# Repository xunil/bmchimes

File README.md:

Controller firmware for ESP8266 modules for Burning Man chimes project.

Using RtcDS3231 library https://github.com/Makuna/Rtc/

TODO:
* WiFi improvements
  * Add config keys for at least 3 WiFi networks and SSIDs
  * Attempt to join each in series for 20 seconds at a time
  * If all three fail, become AP instead
  * Add option to go straight to AP mode
* Add ADC measurement and recording for battery voltage
* Defaults for config

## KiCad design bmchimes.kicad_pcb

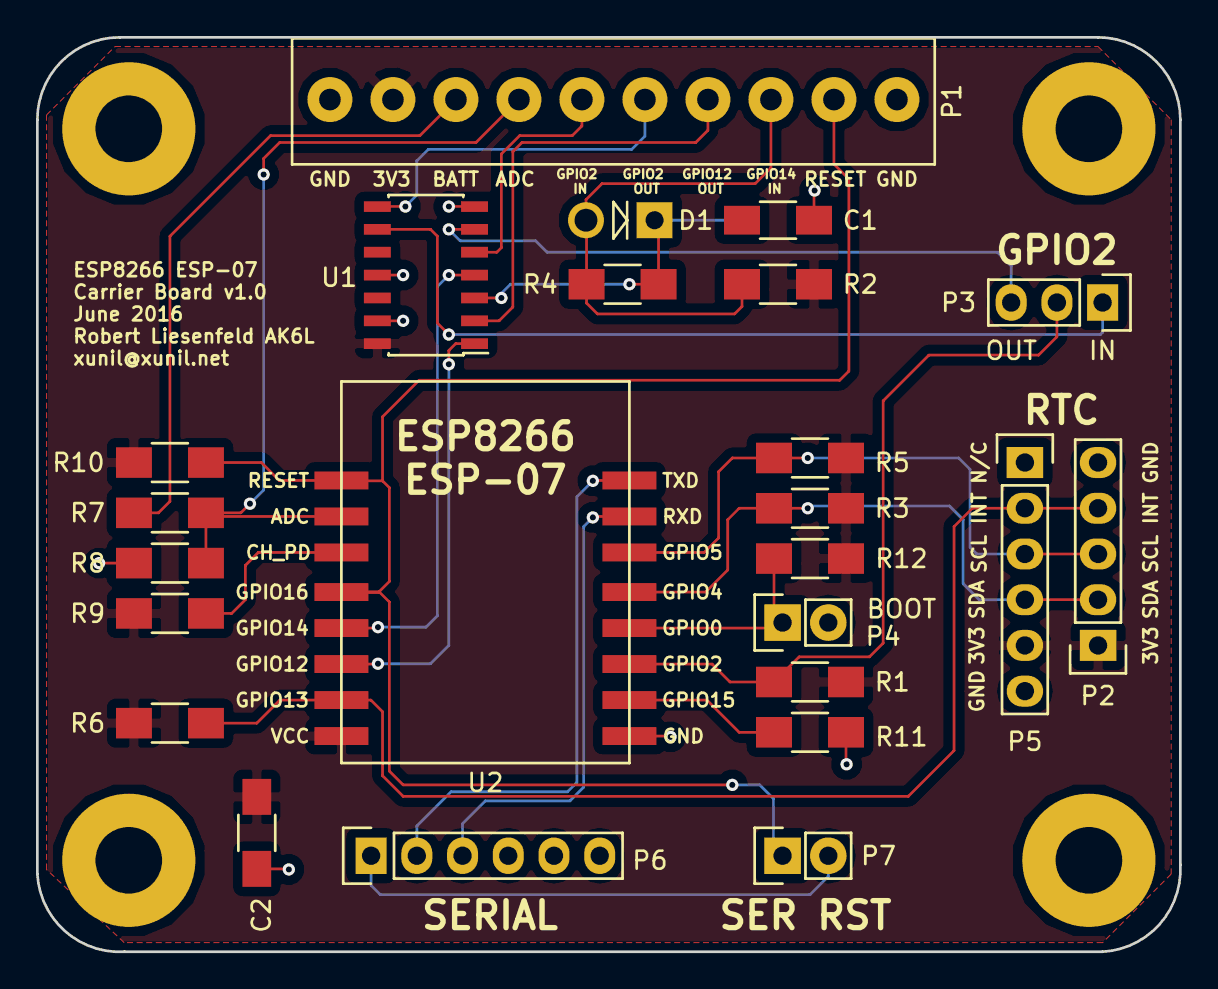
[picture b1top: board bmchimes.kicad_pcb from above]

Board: 2 copper layers, 63.5 x 50.8 mm, 28 parts (0 on the bottom side), 24 nets.

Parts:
C1, C2: C; C_1206_HandSoldering
D1: D; Diode_DO-41_SOD81_Vertical_AnodeUp
P1: CONN_01X10; Adafruit_3.5mm_Terminal_Block
P2: CONN_01X05; Pin_Header_Straight_1x05
P3: CONN_02X03; Pin_Header_Straight_1x03
P4, P7: CONN_01X02; Pin_Header_Straight_1x02
P5, P6: CONN_01X06; Pin_Header_Straight_1x06
P8, P9, P10, P11: CONN_01X01; MountingHole_3.7mm_Pad
R1, R2, R3, R4, R5, R6, R7, R8, R9, R10, R11, R12: R; R_1206_HandSoldering
U1: 74HC7014; SOIC-14_3.9x8.7mm_Pitch1.27mm
U2: ESP07

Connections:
3V3: C2.1, P1.2, P2.1, P5.5, R1.1, R2.2, R3.1, R5.1, R6.1, R9.1, R10.1, R12.1, U1.14, U2.16
ADC: P1.4, R7.2, R8.1, U2.10
BATT: P1.3, R7.1
GND: C1.2, C2.2, P1.1, P1.10, P2.5, P4.2, P5.6, P6.6, P8.1, P9.1, P10.1, P11.1, R8.2, R11.2, U1.7, U1.11, U1.13, U2.1
GPIO2: P3.2, R1.2, U2.3
GPIO2_IN: P1.5, U1.5
GPIO2_IN_ST: P3.3, U1.6
GPIO2_OUT: P3.1, U1.9
GPIO2_OUT_ST: P1.6, U1.8
GPIO4: P2.2, P5.4, R3.2, U2.5
GPIO5: P2.3, P5.3, R5.2, U2.6
GPIO12: U1.1, U2.14
GPIO12_OUT: P1.7, U1.2
GPIO13: P2.4, P5.2, R6.2, U2.15
GPIO14: U1.4, U2.13
GPIO14_IN: D1.2, P1.8, R2.1, R4.2
GPIO14_IN_DB: C1.1, D1.1, R4.1, U1.3
unnamed: P4.1, R12.2, U2.4
unnamed: R9.2, U2.11
unnamed: R11.1, U2.2
RESET: P1.9, P7.1, R10.2, U2.9, U2.12
RESET_SER: P6.1, P7.2
RXD: P6.3, U2.7
TXD: P6.2, U2.8

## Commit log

2016-03-29 Initial import: Lots of basic functionality working. Need to add scheduled GPIO triggering.
2016-03-29 Switched to Rtc library from https://github.com/Makuna/Rtc
2016-04-08 Config read from SPIFFS working
2016-04-10 Added config write, status page, reset button
2016-04-11 Added device description field, chime offset field, home buttons; reset page now refreshes automatically
2016-04-13 Beginning to add sleep and chime timing
2016-04-14 WIP: Sleep and chime timing
2016-04-15 WIP: Still trying to figure out wake/sleep cycle timing
2016-04-22 Updated TODOs, generalized time string construction
2016-04-24 WIP: Calculating wake and sleep
2016-05-01 Finally have RTC alarm working, and sleep alarm calculation appears to be functional as well.
2016-05-10 Finishing up this branch, which has incorporated far more than just config parsing.
2016-05-12 Now using alarm 2 for chime indication; first stab at making sure we're not asleep when it's time to chime
2016-05-15 Fixing compile errors
2016-05-24 Chime timing and stop switch detection is working.
2016-05-25 Fixed bug in handleConfig with handling of checkboxes.
2016-05-30 First effort at a carrier board for the ESP07.
2016-06-01 Added buffer chip to schematic
2016-06-04 ERC passes
2016-06-04 WIP: Pin header layout
2016-06-06 Reworked some of the pull-ups and re-annotated.
2016-06-07 Added footprint for ESP07
2016-06-09 Basic layout complete, ground and power zones defined.
2016-06-10 Zero unconnected nets, calling it done
2016-06-11 Silkscreen changes, sent board to OSH Park
2016-06-15 Added values, ordered parts
2016-06-27 Builds but fundamentally flawed logic: Need to return to RTC alarm-based chime timing and use once-a-minute alarm for non-critical events such as sleep and statistics tracking
2016-06-27 Option-izing the chime stop chiming
2016-06-27 Switched back to chimes being triggered by an RTC alarm; still need to add chime repetition and hours chiming; sleeping and stats collection triggered by once-per-minute alarm.
2016-07-01 Many fixes and features: - Separated chiming back onto its own alarm. - Added chime testing page. - Added default config when config not found on SPIFFS. - Added WiFi AP mode. - Default configuration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
2016-07-01 Minor fixes to debug output; added logic to skip a scheduled chime if a manual one is in progress; fixed issue with AP mode.
2016-07-03 Removed some superfluous debugging info and added an automatic refresh to the stats page.
2016-07-04 - Updated root page to display next chime, next sleep, and correct temperature. - Syncing with NTP and writing to RTC will now cause sleep and chime timing to be recalculated. - Added ability to clea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
2016-07-05 No idea why, but twiddling the LED in the stop switch ISR seems to have fixed the issue.
2016-07-06 Don't handle web requests while chiming as it interferes with interrupt response times, such as for the chime stop switch.
2016-07-06 Added chime duration stats collection.
2016-07-06 Fixed statistics collection for chime duration.
2016-07-19 Turns out rewriting a 1400+ line file to slow flash takes about 5 or 6 seconds, so we just won't do that while chiming. Future enhancement: set a flag to collect stats, collect after chime finished.
2016-07-22 Removed some unnecessary headers, switched from #defines to consts, rearranged some header includes, and got the heartbeat working (sort of).
2016-07-23 Fixing stats collection bug
2016-07-24 Maybe we can handle web requests while chiming after all.
2016-07-30 Heartbeat blip now fires every 15 sec.
2016-07-30 Ad hoc network now starts with a password
2016-07-30 Added sanity check so the module never goes into a permanent sleep.
2016-07-31 Bugfixes and added configuration options, including: - Added config option to enable/disable heartbeat LED on pin 2 - Added config option for inter-chime delay, in preparation for sequential chime - 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
2016-08-01 All timing in seconds (except for stop switch timeout, which is in ms), also added chime sequence and hour chime.
2016-08-02 Updating example config to reflect updated options
2016-08-04 First stab at absolute timing for the chime delays; the chimes should start N seconds after the last chime started, not after the last chime -ended-
2016-08-06 Switched to model where chime schedule is calculated ahead of time. Schedule is checked for validity when once-per-minute alarm fires, and if invalid, is recalculated. Still appear to have bugs with 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
2016-08-07 Overrode HardwareSerial to provide a mechanism for buffering all text written to the serial port in a circular buffer, so the serial debug can be displayed in the web UI. Miraculously, it compiles.
2016-08-07 Enlarged TeeSerial buffer to 2 kilobytes; switched all debugging output to use streaming form (<<) rather than print/println calls. Added some debugging for stats collection.
2016-08-11 Added device description to page titles; added auto-refreshing page for debug log; more attempts at perfecting chime schedule calculation.
2016-08-14 WIP: Switching to scheduling algorithm with parameters of N chimes, M of N, and cycle interval.
2016-08-14 Ruby prototype for new scheduling algorithm
2016-08-14 Removed now-unused configuration elements, deleted a couple unused variables, removed the enum for chime state since it's not relevant outside of schedule calculation.
2016-08-15 Added parameters for chime N of M, put the stop switch interval on the front page, and added a ton of debug in the chime schedule function.
2016-08-15 Removed obnoxious debugging from scheduleChimeSequence()
2016-08-15 WIP: Detecting sleep overlap with chime schedule.
2016-08-17 Spelling error, and some debug code for the sleep time calculation.
2016-08-20 Many changes, including: Styling changes to config and root pages. Adoption of StringStream to simplify HTML generation and other things. Added ability to disable chiming. Added another tunable for t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
2016-08-21 Reporting progress less often to avoid slowing down OTA update.
2016-08-21 Changed chime schedule algorithm to bring the initial chimes closer together, and to add a couple 'silent' strike intervals. Also exposed the chime number in the root page.
2016-11-18 Hard-coded fifteen minute chime.
2016-11-18 Commenting out fifteen minute chime for now.
2016-11-18 DST offset goes the other way, apparently
2016-11-18 Added handling for DST.
2016-11-18 Adding SSDP and mDNS support.
2016-11-19 ifdef-ing out initial chimes, so the firmware will just chime the hours.
